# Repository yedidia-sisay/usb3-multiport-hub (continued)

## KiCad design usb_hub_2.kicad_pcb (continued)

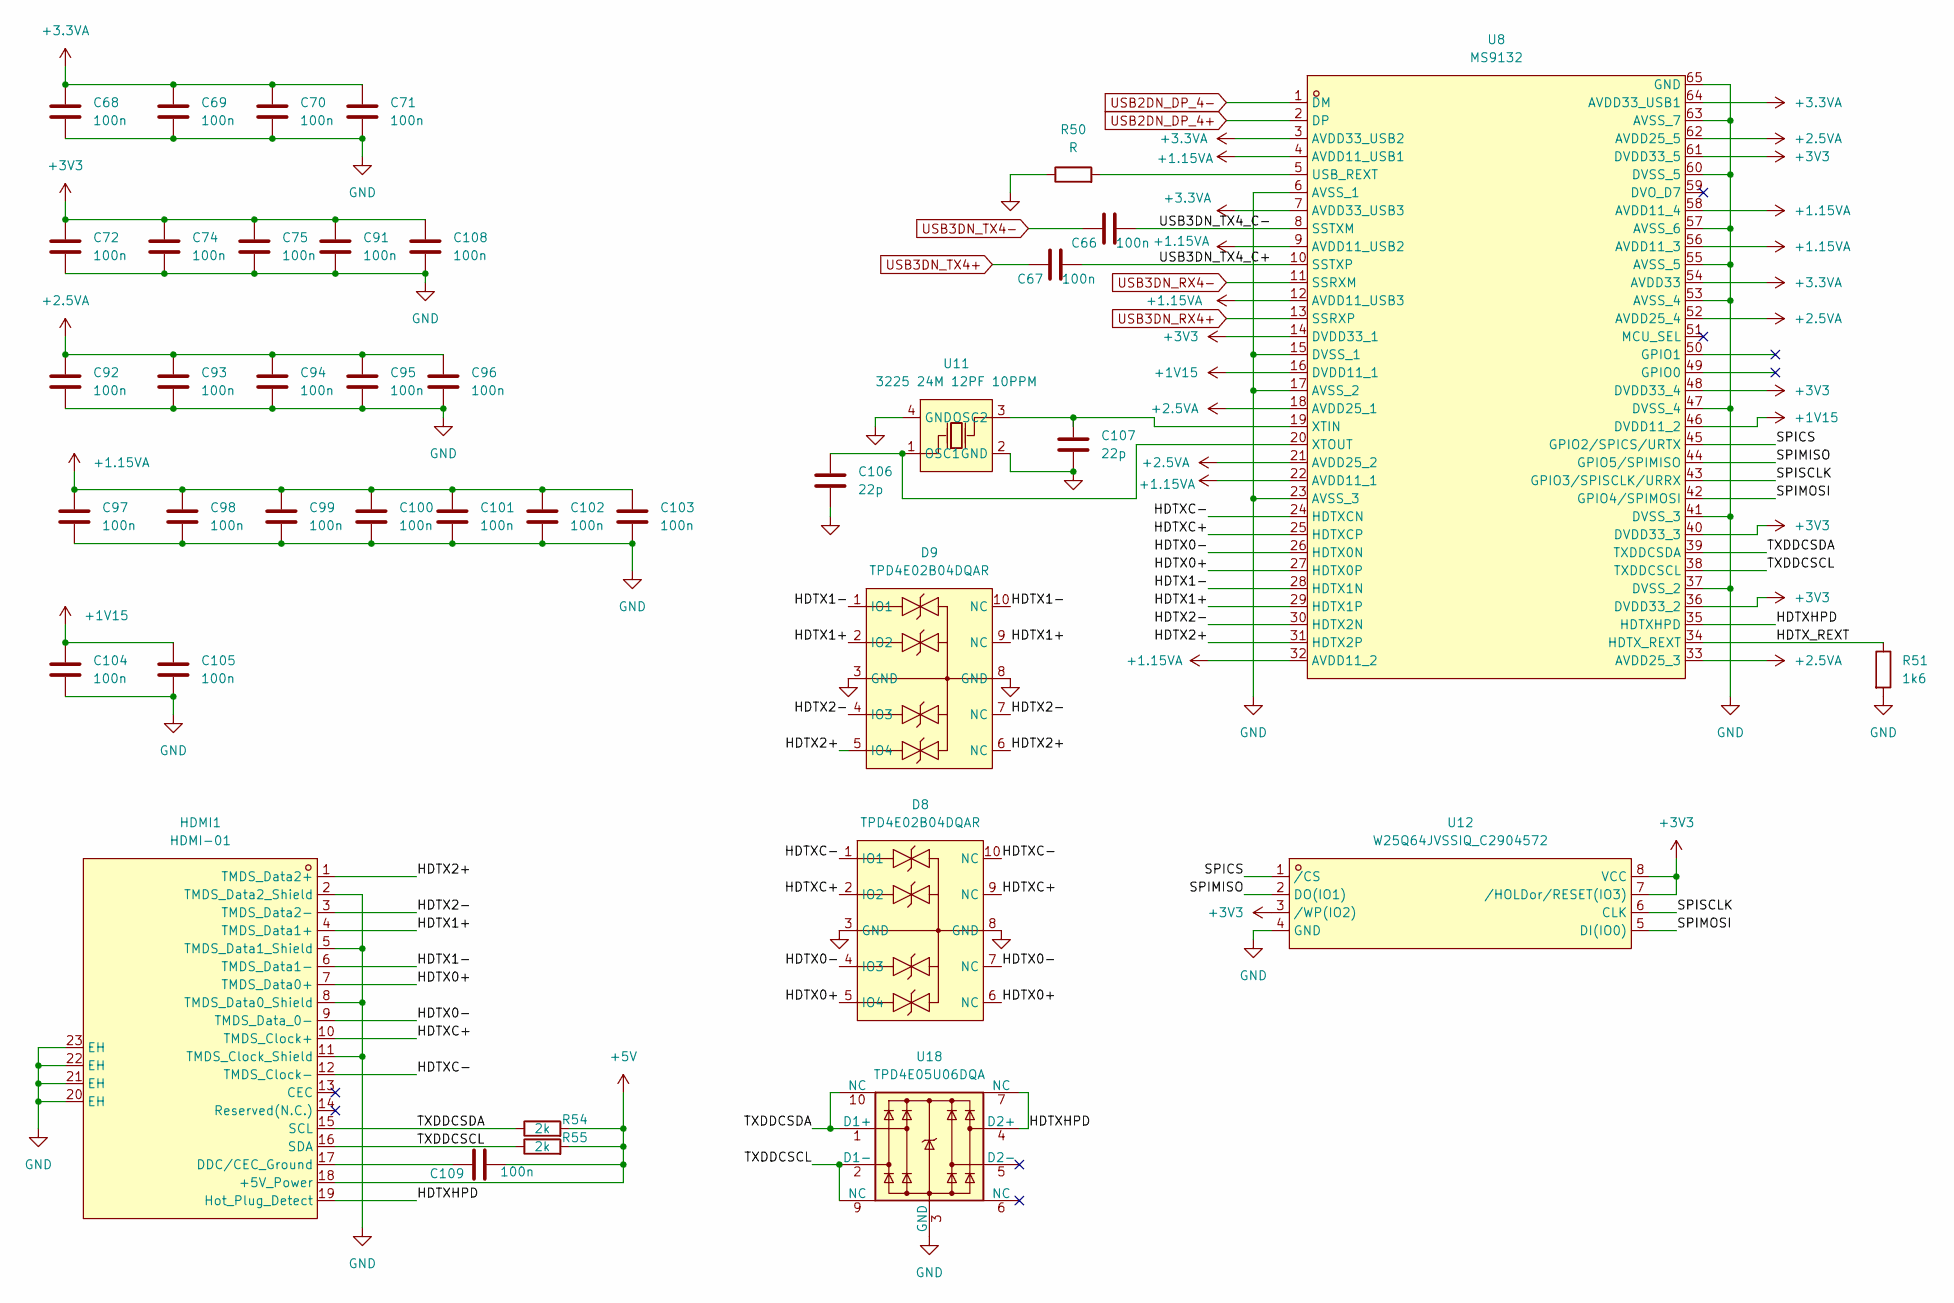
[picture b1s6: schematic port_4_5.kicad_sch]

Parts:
C66, C67, C68, C69, C70, C71, C72, C74, C75, C91, C92, C93, C94, C95, C96, C97, C98, C99, C100, C101, C102, C103, C104, C105, C108, C109: 100n; C_0402_1005Metric
C106, C107: 22p; C_0402_1005Metric
D8, D9: TPD4E02B04DQAR; USON-10_L2.5-W1.0-P0.50-BL; MPN TPD4E02B04DQAR; LCSC Part C106794
HDMI1: HDMI-01; USB-SMD_HDMI-01; MPN HDMI-01; LCSC Part C2906135
R50: R; R_0402_1005Metric
R51: 1k6; R_0402_1005Metric
R54, R55: 2k; R_0402_1005Metric
U8: MS9132; QFN-64_L9.0-W9.0-P0.50-TL-EP5.7; MPN MS9132; LCSC Part C5273789
U11: 3225 24M 12PF 10PPM; CRYSTAL-SMD_4P-L3.2-W2.5-BL; MPN 3225 24M 12PF 10PPM; LCSC Part C5181479
U12: W25Q64JVSSIQ_C2904572; SOP-8_L5.3-W5.3-P1.27-LS8.0-BL; MPN W25Q64JVSSIQ; LCSC Part C2904572
U18: TPD4E05U06DQA; USON-10_2.5x1.0mm_P0.5mm

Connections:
+1.15VA: C97.1, C98.1, C99.1, C100.1, C101.1, C102.1, C103.1, U8.4 (AVDD11_USB1), U8.9 (AVDD11_USB2), U8.12 (AVDD11_USB3), U8.22 (AVDD11_1), U8.32 (AVDD11_2), U8.56 (AVDD11_3), U8.58 (AVDD11_4); also elsewhere on the board
+1V15: C104.1, C105.1, U8.16 (DVDD11_1), U8.46 (DVDD11_2); also elsewhere on the board
+2.5VA: C92.1, C93.1, C94.1, C95.1, C96.1, U8.18 (AVDD25_1), U8.21 (AVDD25_2), U8.33 (AVDD25_3), U8.52 (AVDD25_4), U8.62 (AVDD25_5); also elsewhere on the board
+3.3VA: C68.1, C69.1, C70.1, C71.1, U8.3 (AVDD33_USB2), U8.7 (AVDD33_USB3), U8.54 (AVDD33), U8.64 (AVDD33_USB1); also elsewhere on the board
+3V3: C72.1, C74.1, C75.1, C91.1, C108.1, U8.14 (DVDD33_1), U8.36 (DVDD33_2), U8.40 (DVDD33_3), U8.48 (DVDD33_4), U8.61 (DVDD33_5), U12.3 (/WP(IO2)), U12.7 (/HOLDor/RESET(IO3)), U12.8 (VCC); also elsewhere on the board
+5V: C109.2, HDMI1.18 (+5V_Power), R54.2, R55.2; also elsewhere on the board
/HDMI/HDTX0+: D8.5 (IO4), D8.6 (NC), HDMI1.7 (TMDS_Data0+), U8.27 (HDTX0P)
/HDMI/HDTX0-: D8.4 (IO3), D8.7 (NC), HDMI1.9 (TMDS_Data_0-), U8.26 (HDTX0N)
/HDMI/HDTX1+: D9.2 (IO2), D9.9 (NC), HDMI1.4 (TMDS_Data1+), U8.29 (HDTX1P)
/HDMI/HDTX1-: D9.1 (IO1), D9.10 (NC), HDMI1.6 (TMDS_Data1-), U8.28 (HDTX1N)
/HDMI/HDTX2+: D9.5 (IO4), D9.6 (NC), HDMI1.1 (TMDS_Data2+), U8.31 (HDTX2P)
/HDMI/HDTX2-: D9.4 (IO3), D9.7 (NC), HDMI1.3 (TMDS_Data2-), U8.30 (HDTX2N)
/HDMI/HDTXC+: D8.2 (IO2), D8.9 (NC), HDMI1.10 (TMDS_Clock+), U8.25 (HDTXCP)
/HDMI/HDTXC-: D8.1 (IO1), D8.10 (NC), HDMI1.12 (TMDS_Clock-), U8.24 (HDTXCN)
/HDMI/HDTXHPD: HDMI1.19 (Hot_Plug_Detect), U8.35 (HDTXHPD), U18.4 (D2+), U18.7 (NC)
/HDMI/HDTX_REXT: R51.1, U8.34 (HDTX_REXT)
/HDMI/SPICS: U8.45 (GPIO2/SPICS/URTX), U12.1 (/CS)
/HDMI/SPIMISO: U8.44 (GPIO5/SPIMISO), U12.2 (DO(IO1))
/HDMI/SPIMOSI: U8.42 (GPIO4/SPIMOSI), U12.5 (DI(IO0))
/HDMI/SPISCLK: U8.43 (GPIO3/SPISCLK/URRX), U12.6 (CLK)
/HDMI/TXDDCSCL: HDMI1.16 (SDA), R55.1, U8.38 (TXDDCSCL), U18.2 (D1-), U18.9 (NC)
/HDMI/TXDDCSDA: HDMI1.15 (SCL), R54.1, U8.39 (TXDDCSDA), U18.1 (D1+), U18.10 (NC)
/HDMI/USB3DN_TX4_C+: C67.2, U8.10 (SSTXP)
/HDMI/USB3DN_TX4_C-: C66.2, U8.8 (SSTXM)
GND: C68.2, C69.2, C70.2, C71.2, C72.2, C74.2, C75.2, C91.2, C92.2, C93.2, C94.2, C95.2, C96.2, C97.2, C98.2, C99.2, C100.2, C101.2, C102.2, C103.2, C104.2, C105.2, C106.2, C107.2, C108.2, D8.3 (GND), D8.8 (GND), D9.3 (GND), D9.8 (GND), HDMI1.2 (TMDS_Data2_Shield), HDMI1.5 (TMDS_Data1_Shield), HDMI1.8 (TMDS_Data0_Shield), HDMI1.11 (TMDS_Clock_Shield), HDMI1.20 (EH), HDMI1.21 (EH), HDMI1.22 (EH), HDMI1.23 (EH), R50.1, R51.2, U8.6 (AVSS_1), U8.15 (DVSS_1), U8.17 (AVSS_2), U8.23 (AVSS_3), U8.37 (DVSS_2), U8.41 (DVSS_3), U8.47 (DVSS_4), U8.53 (AVSS_4), U8.55 (AVSS_5), U8.57 (AVSS_6), U8.60 (DVSS_5), U8.63 (AVSS_7), U8.65 (GND), U11.2 (GND), U11.4 (GND), U12.4 (GND), U18.3 (GND), U18.8 (GND); also elsewhere on the board
unnamed: C109.1, HDMI1.17 (DDC/CEC_Ground)
unnamed: R50.2, U8.5 (USB_REXT)
unnamed: C106.1, U8.20 (XTOUT), U11.1 (OSC1)
unnamed: C107.1, U8.19 (XTIN), U11.3 (OSC2)
USB2DN_DP_4+: U8.2 (DP); also elsewhere on the board
USB2DN_DP_4-: U8.1 (DM); also elsewhere on the board
USB3DN_RX4+: U8.13 (SSRXP); also elsewhere on the board
USB3DN_RX4-: U8.11 (SSRXM); also elsewhere on the board
USB3DN_TX4+: C67.1; also elsewhere on the board
USB3DN_TX4-: C66.1; also elsewhere on the board

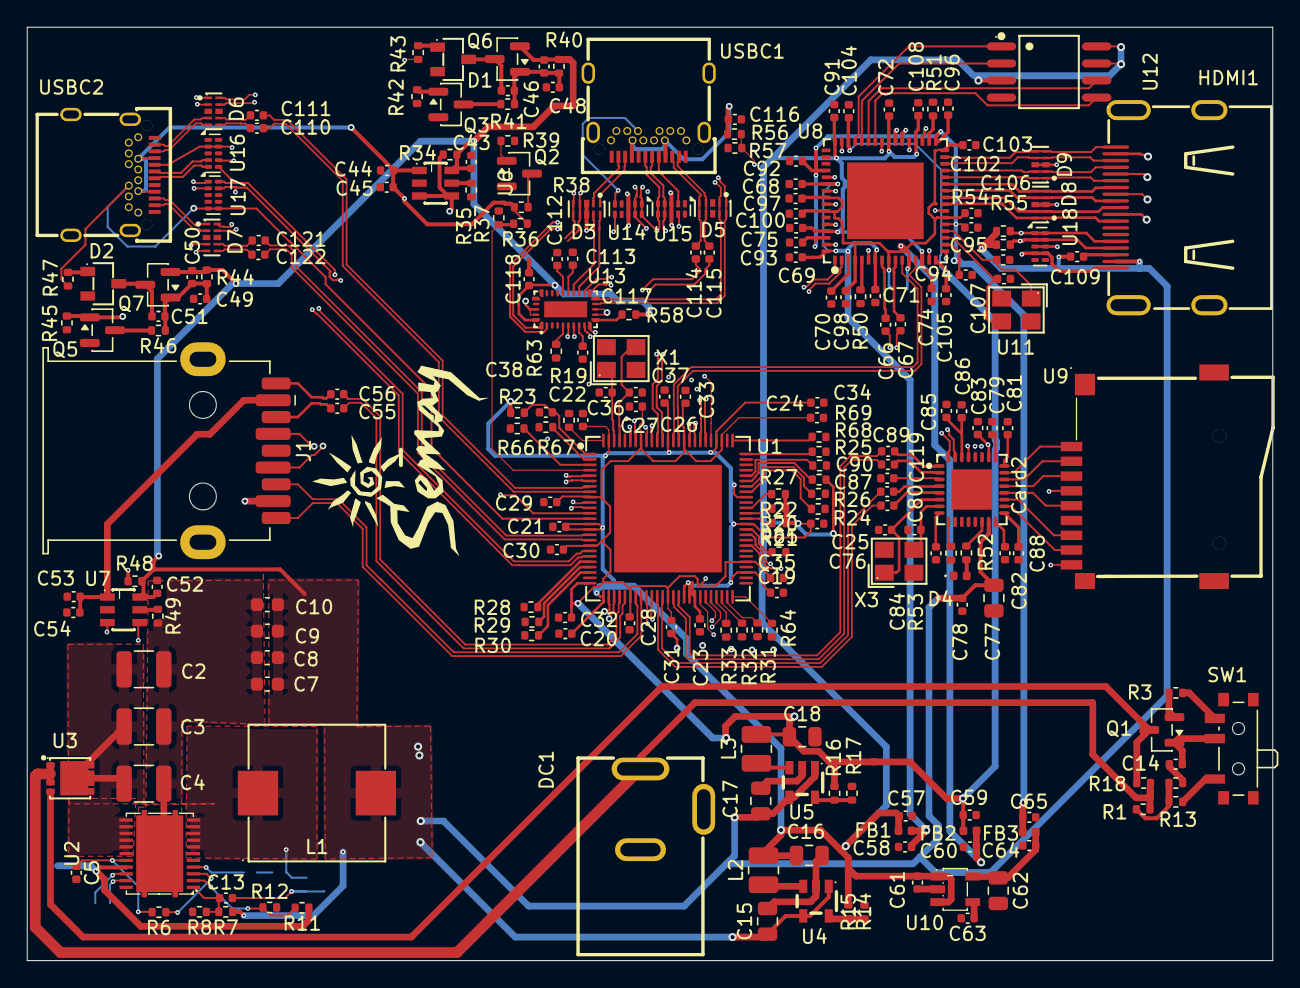
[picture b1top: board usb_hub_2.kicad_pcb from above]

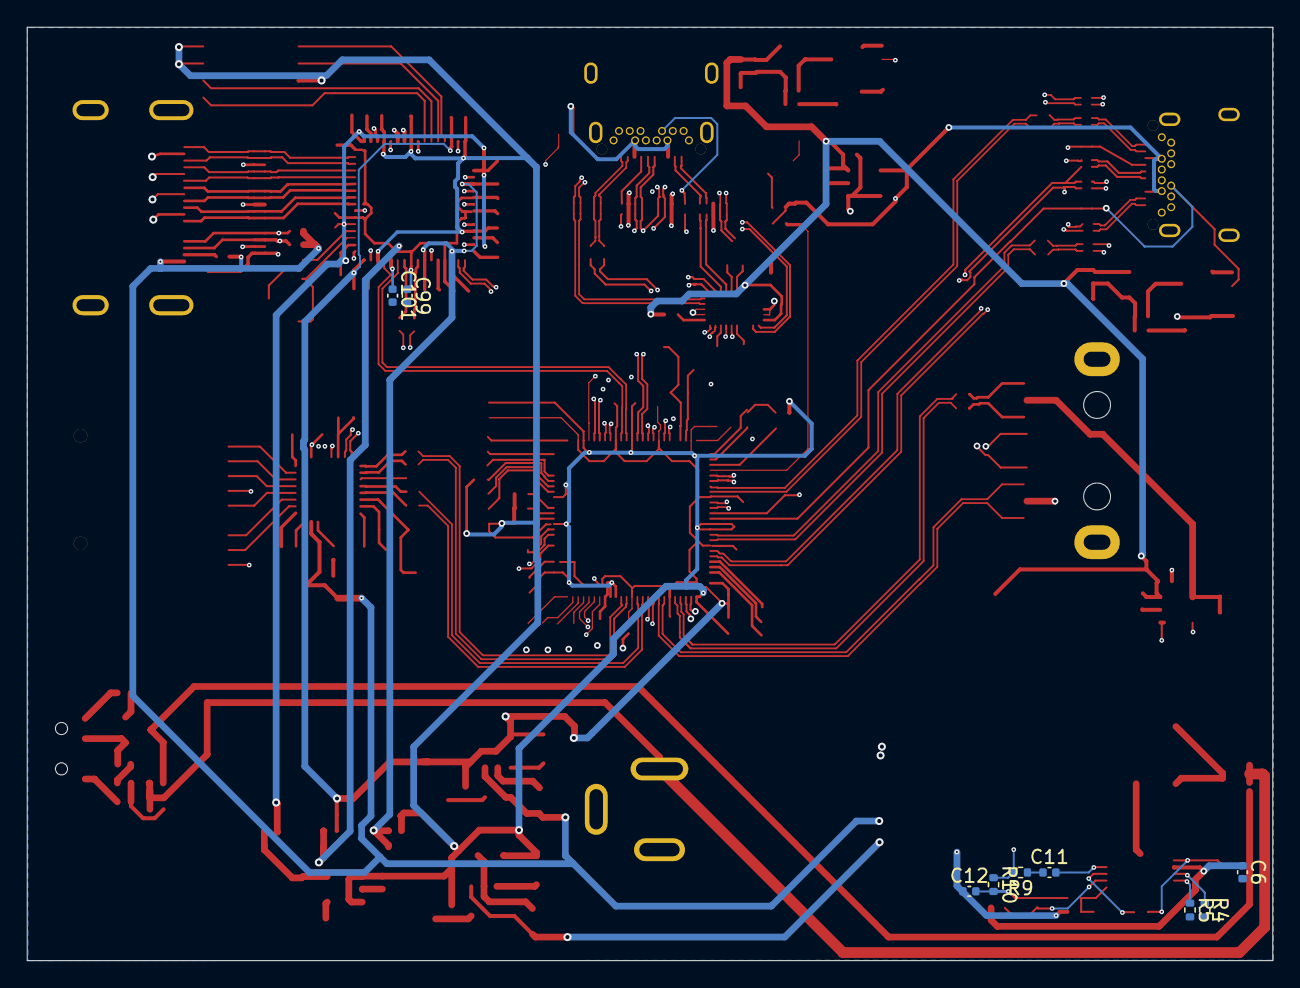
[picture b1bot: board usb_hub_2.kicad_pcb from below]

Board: 6 copper layers, 92.6 x 69.4 mm, 230 parts (9 on the bottom side), 178 nets.

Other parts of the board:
-: LOGO; logo
